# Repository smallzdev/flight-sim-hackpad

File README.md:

# Smallz's Flight Sim Hackpad
This is my flight sim hack pad files :)

I designed this specifically for MSFS 2024. I've always wanted a keyboard like this, so why not make one?

## PCB Layout

## Schematic Layout

## Fully Assembled Model

## Case Images
They will fit together in a sandwich mount style. It'll print using 2 files (top and bottom, the top is on the left and the bottom is on the right in the image below).

## BOM

1 x Seeduno XIAO RP2040
1 x MICROCHIP MCP23017-E/SP Pin Expander
1 x 100nF 50VDC Capacitor
1 x 0.91 inch OLED display (pin order = GND-VCC-SCL-SDA)
2 x EC11E Rotary encoders (with switch)
4 x M3x16mm screws
6 x DSA keycaps
6 x MX-Style switches
1 x PCB

## Feel free to make this for yourself or as a gift :)

## Disclaimer
I haven't tested anything yet to see if it works. Make at your own risk. By using this model you agree that I (as in the creator) am also not responsible for any incidents or issues this causes. It's simply a project I made for fun.

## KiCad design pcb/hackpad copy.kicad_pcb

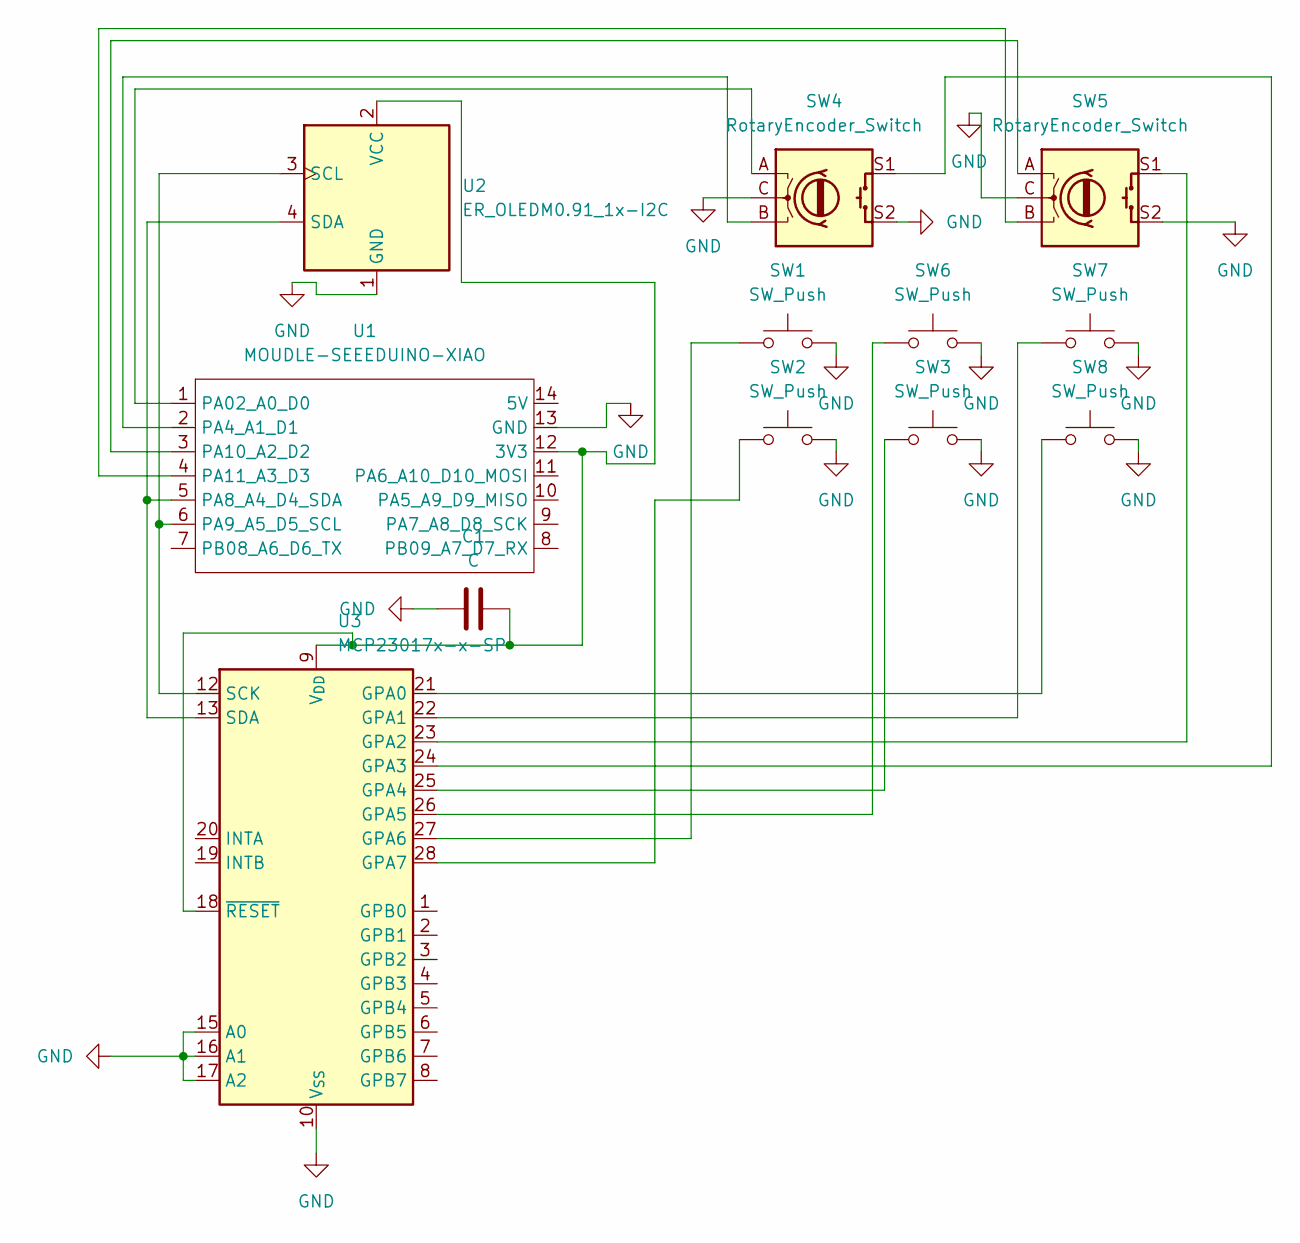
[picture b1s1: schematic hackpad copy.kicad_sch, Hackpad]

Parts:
C1: C; C_Disc_D5.0mm_W2.5mm_P5.00mm
SW1, SW2, SW3, SW6, SW7, SW8: SW_Push; SW_Cherry_MX_1.00u_PCB
SW4, SW5: RotaryEncoder_Switch; RotaryEncoder_Alps_EC11E-Switch_Vertical_H20mm_CircularMoun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
U1: MOUDLE-SEEEDUINO-XIAO; XIAO-Generic-Hybrid-14P-2.54-21X17.8MM
U2: ER_OLEDM0.91_1x-I2C
U3: MCP23017x-x-SP; DIP-28_W7.62mm

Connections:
GND: C1.1, SW1.2, SW2.2, SW3.2, SW4.C, SW4.S2, SW5.C, SW5.S2, SW6.2, SW7.2, SW8.1, U1.13 (GND), U2.1 (GND), U3.10 (V_{SS}), U3.15 (A0), U3.16 (A1), U3.17 (A2)
unnamed: C1.2, U1.12 (3V3), U2.2 (VCC), U3.9 (V_{DD}), U3.18 (~RESET)
unnamed: SW4.A, U1.1 (PA02_A0_D0)
unnamed: SW4.B, U1.2 (PA4_A1_D1)
unnamed: U1.5 (PA8_A4_D4_SDA), U2.4 (SDA), U3.13 (SDA)
unnamed: U1.6 (PA9_A5_D5_SCL), U2.3 (SCL), U3.12 (SCK)
unnamed: SW5.A, U1.3 (PA10_A2_D2)
unnamed: SW5.B, U1.4 (PA11_A3_D3)
unnamed: SW8.2, U3.21 (GPA0)
unnamed: SW7.1, U3.22 (GPA1)
unnamed: SW5.S1, U3.23 (GPA2)
unnamed: SW4.S1, U3.24 (GPA3)
unnamed: SW3.1, U3.25 (GPA4)
unnamed: SW6.1, U3.26 (GPA5)
unnamed: SW1.1, U3.27 (GPA6)
unnamed: SW2.1, U3.28 (GPA7)

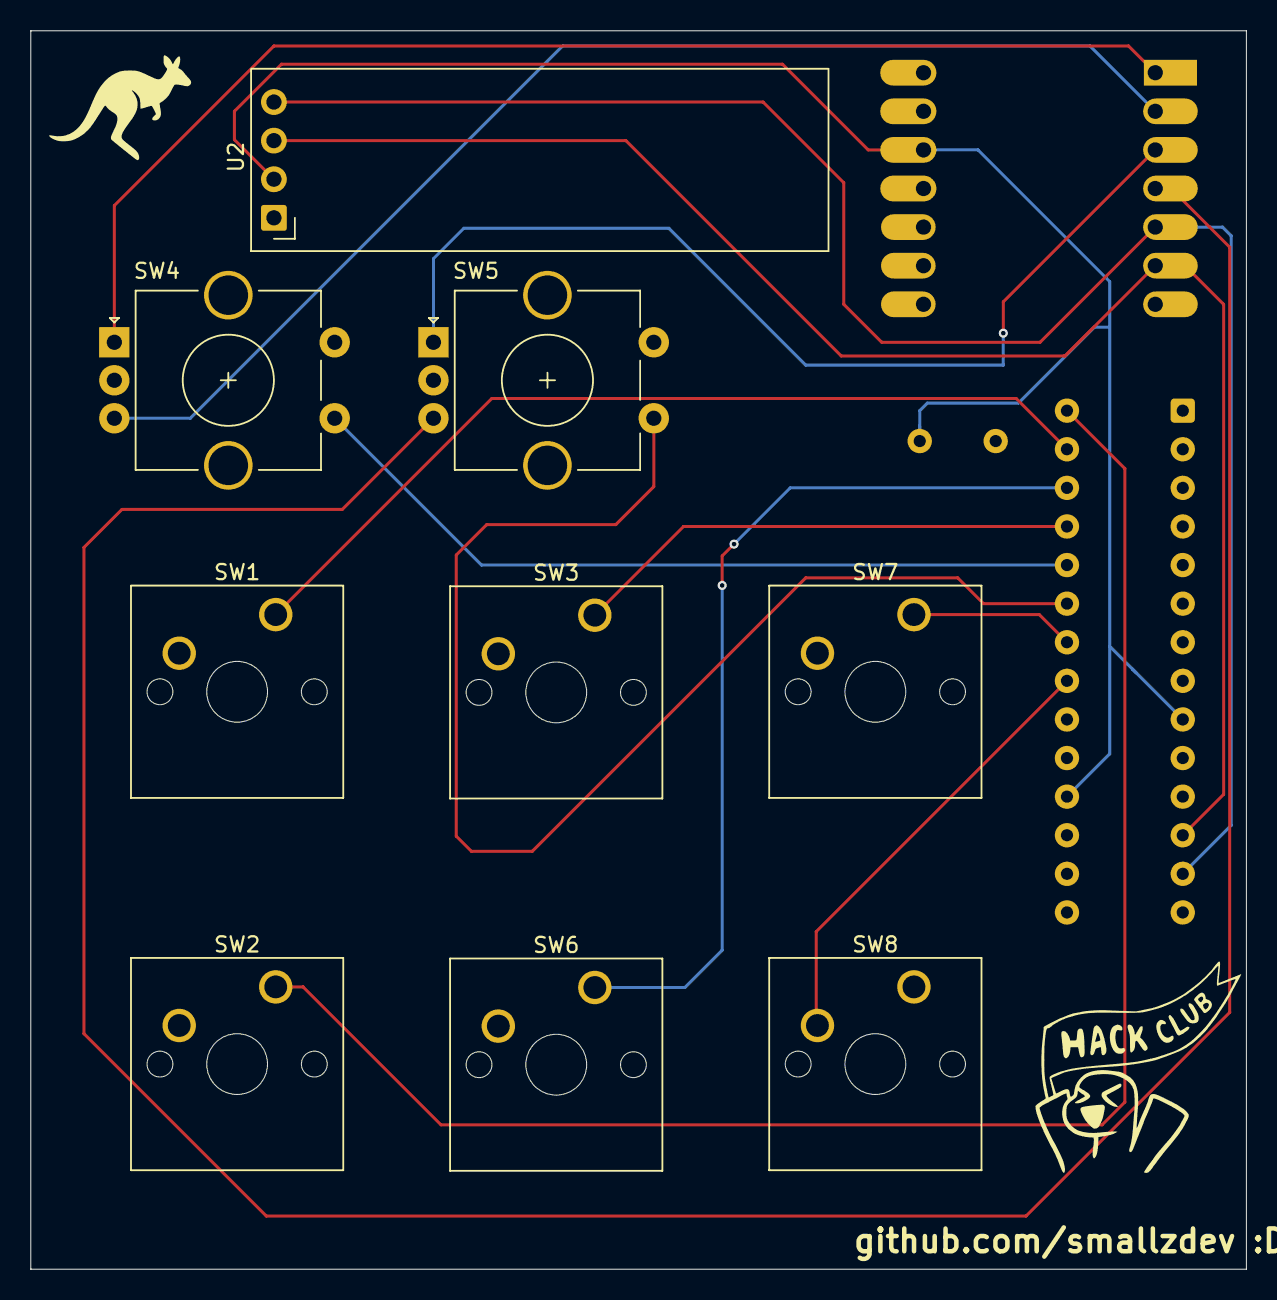
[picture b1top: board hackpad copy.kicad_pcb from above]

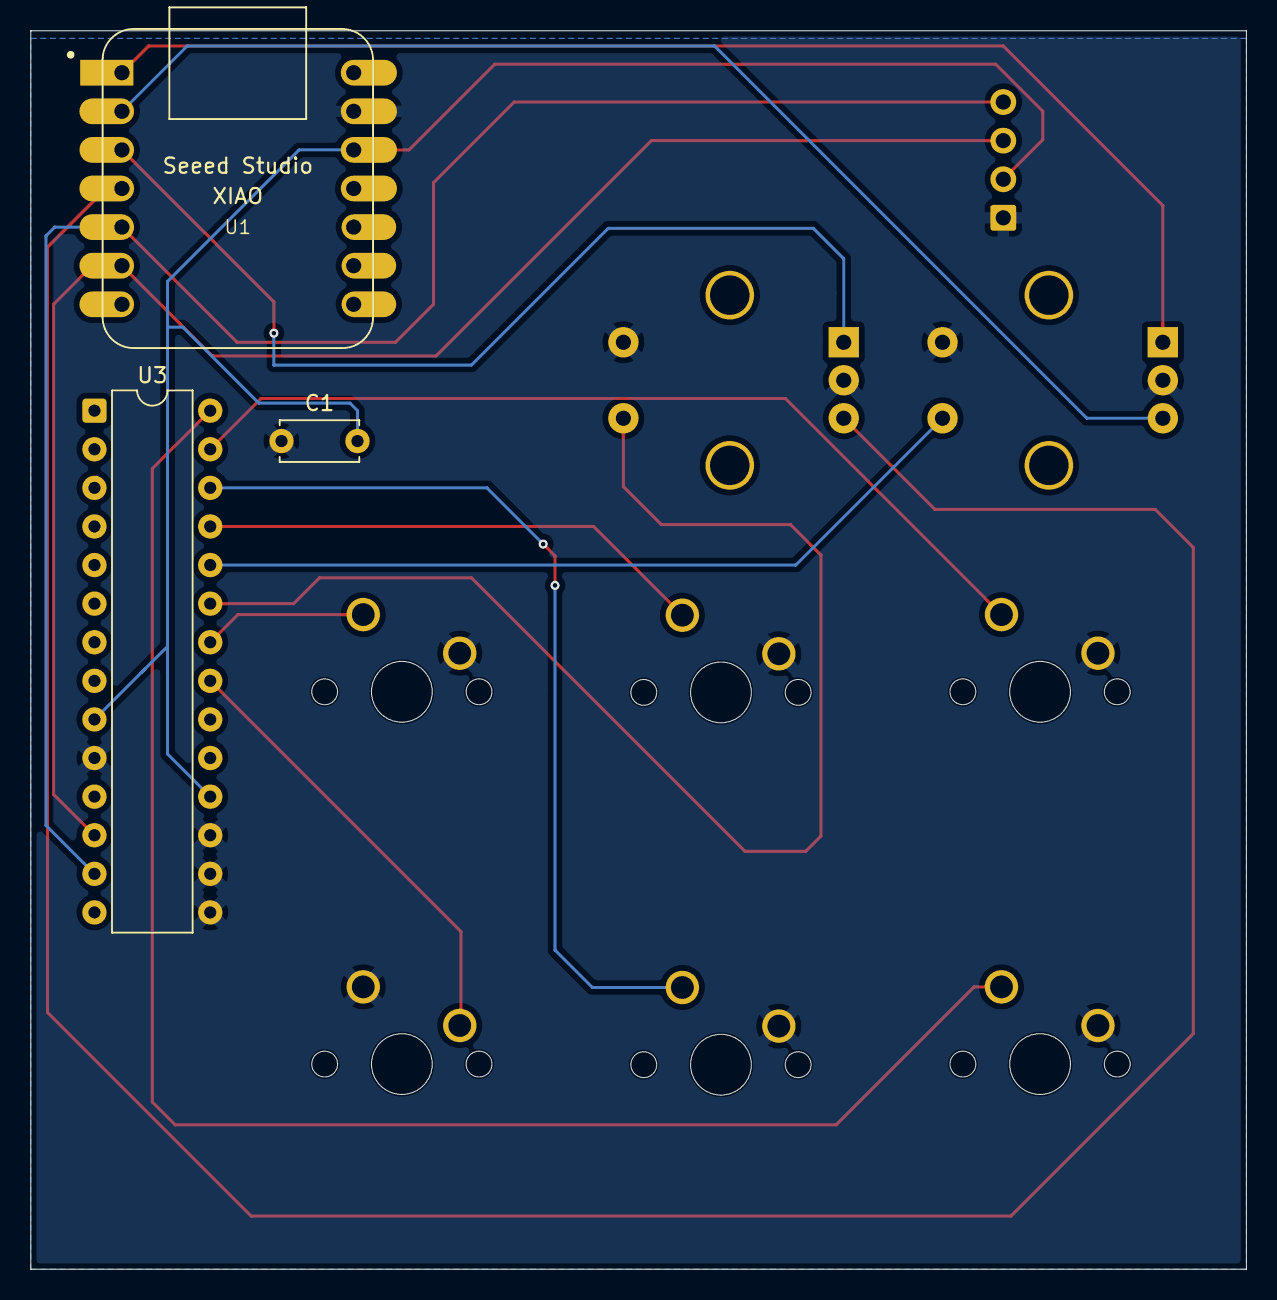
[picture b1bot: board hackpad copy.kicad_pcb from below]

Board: 2 copper layers, 80.0 x 81.5 mm, 12 parts (3 on the bottom side), 16 nets.
